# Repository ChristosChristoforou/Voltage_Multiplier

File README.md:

# Voltage_Multiplier
An implementation of the Cockcroft–Walton multiplier in Kicad, with a ready to build pcb layout

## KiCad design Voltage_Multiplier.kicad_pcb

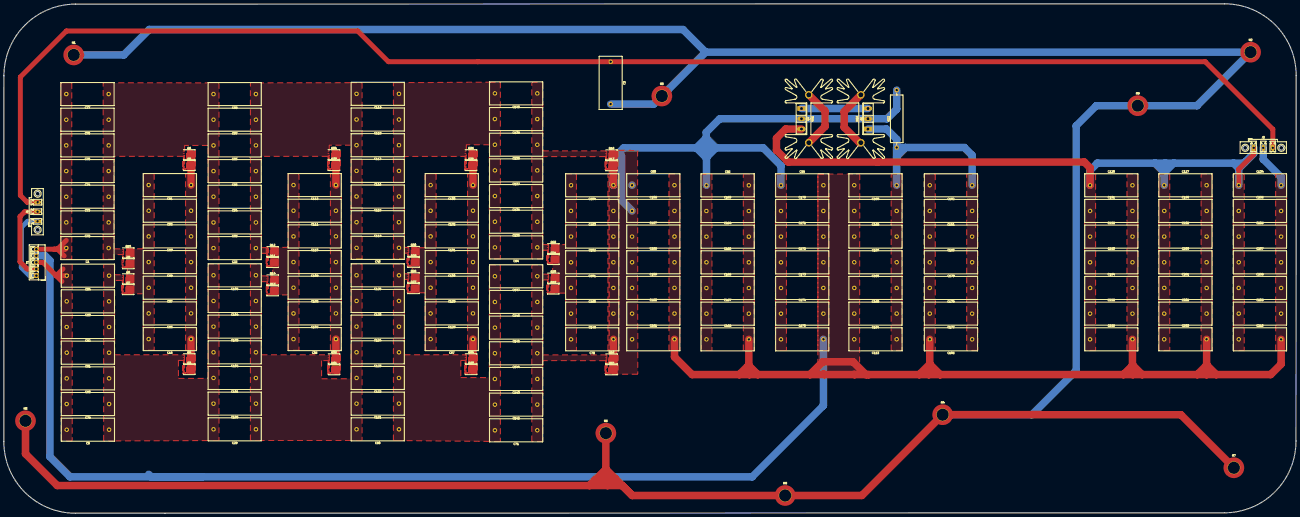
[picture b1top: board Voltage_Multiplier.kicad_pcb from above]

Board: 2 copper layers, 685.9 x 270.4 mm, 190 parts (0 on the bottom side), 38 nets.

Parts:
C1, C8, C15, C22, C29, C36, C43, C50, C57, C64, C71, C72, C73, C74, C75, C76, C77, C78, C79, C80, C81, C82, C83, C84, C85, C86, C87, C88, C89, C90, C91, C92, C93, C94, C95, C96, C97, C98, C99, C100, C101, C102, C103, C104, C105, C106, C107, C108, C109, C110, C111, C112, C113, C114, C115, C116, C117, C118, C119, C120, C121, C122, C123, C124, C125, C126, C127, C128, C129, C130, C131, C132, C133, C134, C135, C136, C137, C138, C139, C140, C142, C143, C144, C145, C146, C147, C149, C150, C151, C152, C153, C154, C156, C157, C158, C159, C160, C161, C163, C164, C165, C166, C167, C168, C170, C171, C172, C173, C174, C175, C177, C178, C179, C180, C181, C182, C184, C185, C186, C187, C188, C189, C191, C192, C193, C194, C195, C196, C198, C199, C200, C201, C202, C203, C205, C206, C207, C208, C209, C210: 10u/1kV; C_Rect_L28.0mm_W12.0mm_P22.50mm_MKS4
C2: C; C_Rect_L28.0mm_W12.0mm_P22.50mm_MKS4
H1, H2, H3, H4, H5, H6, H7, H8, H9: MountingHole_Pad; MountingHole_6.4mm_M6_DIN965_Pad_TopBottom
HS1, HS2: Heatsink_Pad; Heatsink_Fischer_SK129-STS_42x25mm_2xDrill2.5mm
J1, J2: Conn_01x03_Female; PhoenixContact_MCV_1,5_3-GF-5.08_1x03_P5.08mm_Vertical_Thre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
Q1, Q2: IRG4PF50W; TO-247-3_Vertical
Q3, Q4, Q5, Q6, Q7, Q8, Q9, Q10, Q11, Q12, Q13, Q14, Q15, Q16, Q17, Q18, Q19, Q20, Q21, Q22, Q23, Q24, Q25, Q26, Q27, Q28, Q29, Q30, Q31, Q32, Q33, Q34: BSC13DN30NSFD; TDSON-8-1
R22: R_US; R_Axial_Power_L25.0mm_W6.4mm_P30.48mm
T1: 2.4:1_Center_Tapped_20A; TerminalBlock_4Ucon_1x05_P3.50mm_Vertical

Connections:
/Sheet6123FA73/AC1: J1.1, T1.1
/Sheet6123FA73/AC2: J1.2, T1.2
/Sheet6123FA73/GND: C15.2, C85.2, C86.2, C87.2, C88.2, C89.2, C90.2, C91.2, C92.2, C99.2, C106.2, C113.2, C120.2, C127.2, C134.2, C156.2, C157.2, C158.2, C159.2, C160.2, C161.2, C163.2, C164.2, C165.2, C166.2, C167.2, C168.2, C170.2, C171.2, C172.2, C173.2, C174.2, C175.2, C177.2, C178.2, C179.2, C180.2, C181.2, C182.2, C184.2, C185.2, C186.2, C187.2, C188.2, C189.2, C191.2, C192.2, C193.2, C194.2, C195.2, C196.2, C198.2, C199.2, C200.2, C201.2, C202.2, C203.2, C205.2, C206.2, C207.2, C208.2, C209.2, C210.2, J2.2, Q7.4, Q7.5, Q8.5, Q9.4, Q9.5, Q10.5, T1.4
/Sheet6123FA73/Vo: C120.1, C127.1, C134.1, C191.1, C192.1, C193.1, C194.1, C195.1, C196.1, C198.1, C199.1, C200.1, C201.1, C202.1, C203.1, C205.1, C206.1, C207.1, C208.1, C209.1, C210.1, J2.1, Q2.3
/Sheet6123FA73/sheet61244BDA/C1: C1.2, C72.2, C73.2, C74.2, C75.2, C76.2, C77.2, T1.5
/Sheet6123FA73/sheet61244BDB/C1: C8.2, C79.2, C80.2, C81.2, C82.2, C83.2, C84.2, T1.3
/Sheet6123FA73/sheet61244BE1/C1: C1.1, C22.2, C72.1, C73.1, C74.1, C75.1, C76.1, C77.1, C93.2, C94.2, C95.2, C96.2, C97.2, C98.2, Q6.1, Q6.2, Q6.3, Q10.1, Q10.2, Q10.3
/Sheet6123FA73/sheet61244BE2/C1: C8.1, C29.2, C79.1, C80.1, C81.1, C82.1, C83.1, C84.1, C100.2, C101.2, C102.2, C103.2, C104.2, C105.2, Q4.1, Q4.2, Q4.3, Q8.1, Q8.2, Q8.3
/Sheet6123FA73/sheet61244BE5/C1: C15.1, C36.2, C86.1, C87.1, C88.1, C89.1, C90.1, C91.1, C107.2, C108.2, C109.2, C110.2, C111.2, C112.2, Q3.4, Q3.5, Q4.5, Q5.4, Q5.5, Q6.5, Q11.4, Q11.5, Q12.5, Q13.4, Q13.5, Q14.5
/Sheet6123FA73/sheet61244BF0/C1: C22.1, C43.2, C93.1, C94.1, C95.1, C96.1, C97.1, C98.1, C114.2, C115.2, C116.2, C117.2, C118.2, C119.2, Q12.1, Q12.2, Q12.3, Q34.1, Q34.2, Q34.3
/Sheet6123FA73/sheet61244BF1/C1: C29.1, C50.2, C100.1, C101.1, C102.1, C103.1, C104.1, C105.1, C121.2, C122.2, C123.2, C124.2, C125.2, C126.2, Q14.1, Q14.2, Q14.3, Q32.1, Q32.2, Q32.3
/Sheet6123FA73/sheet61244BF2/C1: C36.1, C57.2, C107.1, C108.1, C109.1, C110.1, C111.1, C112.1, C128.2, C129.2, C130.2, C131.2, C132.2, C133.2, Q27.4, Q27.5, Q28.5, Q29.4, Q29.5, Q30.5, Q31.4, Q31.5, Q32.5, Q33.4, Q33.5, Q34.5
/Sheet6123FA73/sheet61244BF3/C1: C43.1, C64.2, C114.1, C115.1, C116.1, C117.1, C118.1, C119.1, C135.2, C136.2, C137.2, C138.2, C139.2, C140.2, Q26.1, Q26.2, Q26.3, Q30.1, Q30.2, Q30.3
/Sheet6123FA73/sheet61244BF3/C2: C64.1, C135.1, C136.1, C137.1, C138.1, C139.1, C140.1, Q18.1, Q18.2, Q18.3, Q22.1, Q22.2, Q22.3
/Sheet6123FA73/sheet61244BF4/C1: C50.1, C71.2, C121.1, C122.1, C123.1, C124.1, C125.1, C126.1, C142.2, C143.2, C144.2, C145.2, C146.2, C147.2, Q24.1, Q24.2, Q24.3, Q28.1, Q28.2, Q28.3
/Sheet6123FA73/sheet61244BF4/C2: C71.1, C142.1, C143.1, C144.1, C145.1, C146.1, C147.1, Q16.1, Q16.2, Q16.3, Q20.1, Q20.2, Q20.3
/Sheet6123FA73/sheet61244BF5/C1: C57.1, C78.2, C128.1, C129.1, C130.1, C131.1, C132.1, C133.1, C149.2, C150.2, C151.2, C152.2, C153.2, C154.2, Q19.4, Q19.5, Q20.5, Q21.4, Q21.5, Q22.5, Q23.4, Q23.5, Q24.5, Q25.4, Q25.5, Q26.5
/Sheet6123FA73/sheet61244BF5/C2: C78.1, C85.1, C92.1, C99.1, C149.1, C150.1, C151.1, C152.1, C153.1, C154.1, C156.1, C157.1, C158.1, C159.1, C160.1, C161.1, C163.1, C164.1, C165.1, C166.1, C167.1, C168.1, C170.1, C171.1, C172.1, C173.1, C174.1, C175.1, Q1.2, Q2.2, Q15.4, Q15.5, Q16.5, Q17.4, Q17.5, Q18.5, R22.2
/Sheet6123FA73/sheet61244BF9/C2: C106.1, C113.1, C177.1, C178.1, C179.1, C180.1, C181.1, C182.1, C184.1, C185.1, C186.1, C187.1, C188.1, C189.1, Q1.1, R22.1
unnamed: C2.1, J1.3, J2.3
unnamed: C2.2, H1.1, H2.1, H3.1, H4.1, H5.1, H6.1, H7.1, H8.1, H9.1
unnamed: Q1.3, Q2.1
unnamed: Q3.1, Q3.2, Q3.3, Q4.4
unnamed: Q5.1, Q5.2, Q5.3, Q6.4
unnamed: Q7.1, Q7.2, Q7.3, Q8.4
unnamed: Q9.1, Q9.2, Q9.3, Q10.4
unnamed: Q11.1, Q11.2, Q11.3, Q12.4
unnamed: Q13.1, Q13.2, Q13.3, Q14.4
unnamed: Q15.1, Q15.2, Q15.3, Q16.4
unnamed: Q17.1, Q17.2, Q17.3, Q18.4
unnamed: Q19.1, Q19.2, Q19.3, Q20.4
unnamed: Q21.1, Q21.2, Q21.3, Q22.4
unnamed: Q23.1, Q23.2, Q23.3, Q24.4
unnamed: Q25.1, Q25.2, Q25.3, Q26.4
unnamed: Q27.1, Q27.2, Q27.3, Q28.4
unnamed: Q29.1, Q29.2, Q29.3, Q30.4
unnamed: Q31.1, Q31.2, Q31.3, Q32.4
unnamed: Q33.1, Q33.2, Q33.3, Q34.4
